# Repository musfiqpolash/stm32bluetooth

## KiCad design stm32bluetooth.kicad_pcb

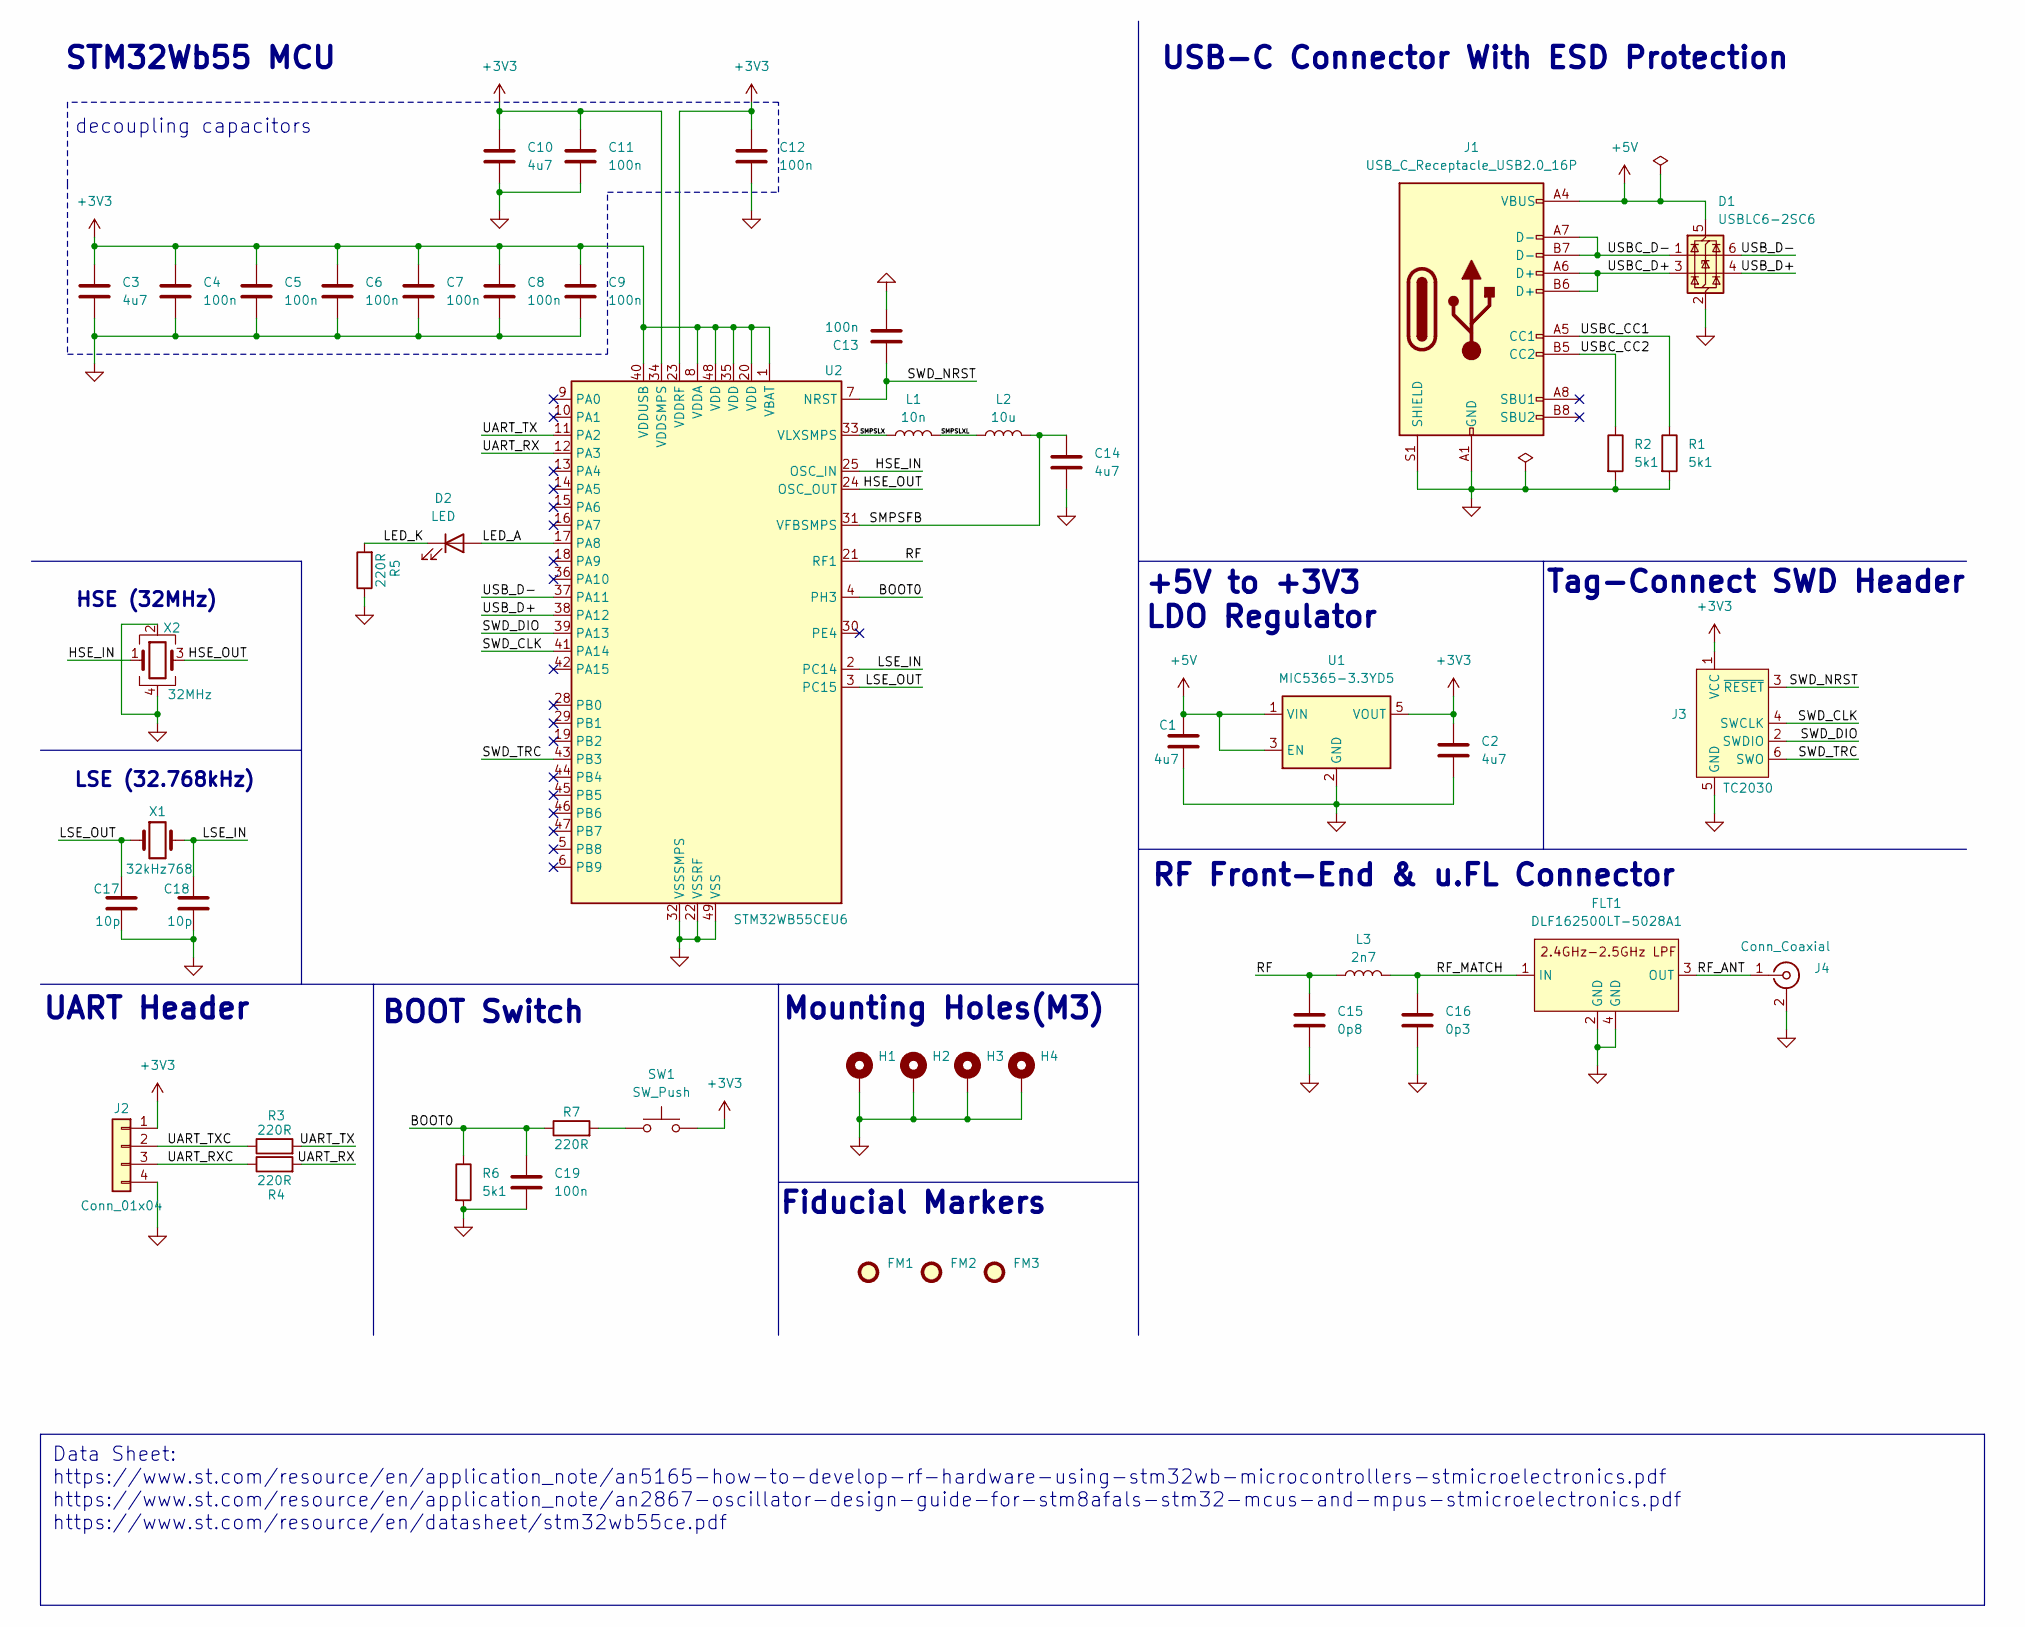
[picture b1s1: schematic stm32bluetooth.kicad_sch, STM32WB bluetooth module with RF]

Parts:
C1, C2, C3, C10, C14: 4u7; C_0603_1608Metric
C4, C5, C6, C7, C8, C9, C11, C12, C13, C19: 100n; C_0402_1005Metric
C15: 0p8; C_0402_1005Metric
C16: 0p3; C_0402_1005Metric
C17, C18: 10p; C_0402_1005Metric
D1: USBLC6-2SC6; SOT-23-6
D2: LED; LED_0402_1005Metric
FLT1: DLF162500LT-5028A1
FM1, FM2, FM3: Fiducial; Fiducial_1mm_Mask2mm
H1, H2, H3, H4: MountingHole_Pad; MountingHole_2.2mm_M2_Pad_Via
J1: USB_C_Receptacle_USB2.0_16P; USB_C_Receptacle_GCT_USB4105-xx-A_16P_TopMnt_Horizontal
J2: Conn_01x04; Molex_PicoBlade_53048-0410_1x04_P1.25mm_Horizontal
J3: TC2030; Tag-Connect_TC2030-IDC-FP_2x03_P1.27mm_Vertical
J4: Conn_Coaxial; U.FL_Hirose_U.FL-R-SMT-1_Vertical
L1: 10n; L_0402_1005Metric
L2: 10u; L_0805_2012Metric
L3: 2n7; L_0402_1005Metric
R1, R2, R6: 5k1; R_0402_1005Metric
R3, R4, R5, R7: 220R; R_0402_1005Metric
SW1: SW_Push; SW_SPST_B3U-1000P-B
U1: MIC5365-3.3YD5; SOT-23-5
U2: STM32WB55CEU6; QFN-48-1EP_7x7mm_P0.5mm_EP5.6x5.6mm
X1: 32kHz768; Crystal_SMD_2012-2Pin_2.0x1.2mm
X2: 32MHz; Crystal_SMD_2016-4Pin_2.0x1.6mm

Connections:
+3V3: C2.1, C3.1, C4.1, C5.1, C6.1, C7.1, C8.1, C9.1, C10.1, C11.1, C12.1, J2.1, J3.1 (VCC), SW1.2, U1.5 (VOUT), U2.1 (VBAT), U2.8 (VDDA), U2.20 (VDD), U2.23 (VDDRF), U2.34 (VDDSMPS), U2.35 (VDD), U2.40 (VDDUSB), U2.48 (VDD)
+5V: C1.1, D1.5 (VBUS), J1.A4 (VBUS), J1.A9 (VBUS), J1.B4 (VBUS), J1.B9 (VBUS), U1.1 (VIN), U1.3 (EN)
/BOOT0: C19.1, R6.1, R7.1, U2.4 (PH3)
/HSE_IN: U2.25 (OSC_IN), X2.1
/HSE_OUT: U2.24 (OSC_OUT), X2.3
/LED_A: D2.2 (A), U2.17 (PA8)
/LED_K: D2.1 (K), R5.2
/LSE_IN: C18.1, U2.2 (PC14), X1.2
/LSE_OUT: C17.1, U2.3 (PC15), X1.1
/RF: C15.1, L3.1, U2.21 (RF1)
/RF_ANT: FLT1.3 (OUT), J4.1 (In)
/RF_MATCH: C16.1, FLT1.1 (IN), L3.2
/SMPSFB: C14.1, L2.2, U2.31 (VFBSMPS)
/SMPSLX: L1.1, U2.33 (VLXSMPS)
/SMPSLXL: L1.2, L2.1
/SWD_CLK: J3.4 (SWCLK), U2.41 (PA14)
/SWD_DIO: J3.2 (SWDIO), U2.39 (PA13)
/SWD_NRST: C13.1, J3.3 (~RESET), U2.7 (NRST)
/SWD_TRC: J3.6 (SWO), U2.43 (PB3)
/UART_RX: R4.2, U2.12 (PA3)
/UART_RXC: J2.3, R4.1
/UART_TX: R3.2, U2.11 (PA2)
/UART_TXC: J2.2, R3.1
/USBC_CC1: J1.A5 (CC1), R1.1
/USBC_CC2: J1.B5 (CC2), R2.1
/USBC_D+: D1.3 (I/O2), J1.A6 (D+), J1.B6 (D+)
/USBC_D-: D1.1 (I/O1), J1.A7 (D-), J1.B7 (D-)
/USB_D+: D1.4 (I/O2), U2.38 (PA12)
/USB_D-: D1.6 (I/O1), U2.37 (PA11)
GND: C1.2, C2.2, C3.2, C4.2, C5.2, C6.2, C7.2, C8.2, C9.2, C10.2, C11.2, C12.2, C13.2, C14.2, C15.2, C16.2, C17.2, C18.2, C19.2, D1.2 (GND), FLT1.2 (GND), FLT1.4 (GND), H1.1, H2.1, H3.1, H4.1, J1.A1 (GND), J1.A12 (GND), J1.B1 (GND), J1.B12 (GND), J1.S1 (SHIELD), J2.4, J3.5 (GND), J4.2 (Ext), R1.2, R2.2, R5.1, R6.2, U1.2 (GND), U2.22 (VSSRF), U2.32 (VSSSMPS), U2.49 (VSS), X2.2, X2.4
unnamed: R7.2, SW1.1

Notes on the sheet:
Data Sheet: https://www.st.com/resource/en/application_note/an5165-how-to-develop-rf-hardware-using-stm32wb-microcontrollers-stmicroelectronics.pdf https://www.st.com/resource/en/application_note/an2867-oscillator-design-guide-for-stm8afals-stm32-mcus-and-mpus-stmicroelectronics.pdf https://www.st.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
HSE (32MHz)
+5V to +3V3 LDO Regulator
decoupling capacitors
USB-C Connector With ESD Protection
STM32Wb55 MCU
Mounting Holes(M3)
BOOT Switch
Tag-Connect SWD Header
Fiducial Markers
RF Front-End & u.FL Connector
LSE (32.768kHz)
UART Header

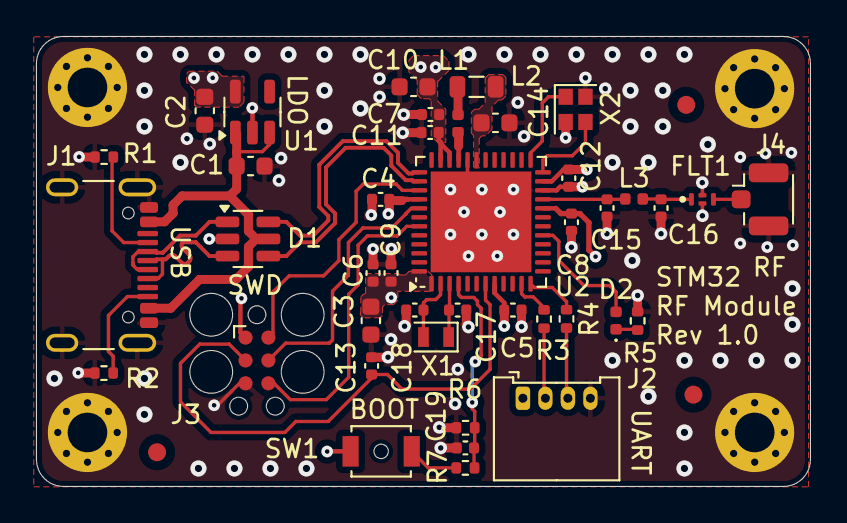
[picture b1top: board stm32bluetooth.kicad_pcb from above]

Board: 4 copper layers, 43.0 x 25.0 mm, 48 parts (0 on the bottom side), 31 nets.

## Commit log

2024-05-09 schematics and pcb
